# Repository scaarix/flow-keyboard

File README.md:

# Flow
An open source split mechanical keyboard powered by [Ergogen](https://github.com/ergogen/ergogen) and kicad
## The board:

# Updates
- REBUILDING THE DESIGN FROM THE GROUND UP
I didn't really like where I was going with this keyboard design and wanted to change the overall look and feel of the keyboard and the features that I want with this board
# Features
- Hotswappable with mx-style switches
- Flippable PCB
- 4 Key Thumb Cluster

## TODO
- [ ] Finish layout (ergogen)
- [ ] Make keyboard outline (ergogen) 
- [ ] Create pcb (ergogen)

# Goals
- Have hotswap with choc, kailh box etc.
- Be wireless
- Have RGB if I can actually configure it properly

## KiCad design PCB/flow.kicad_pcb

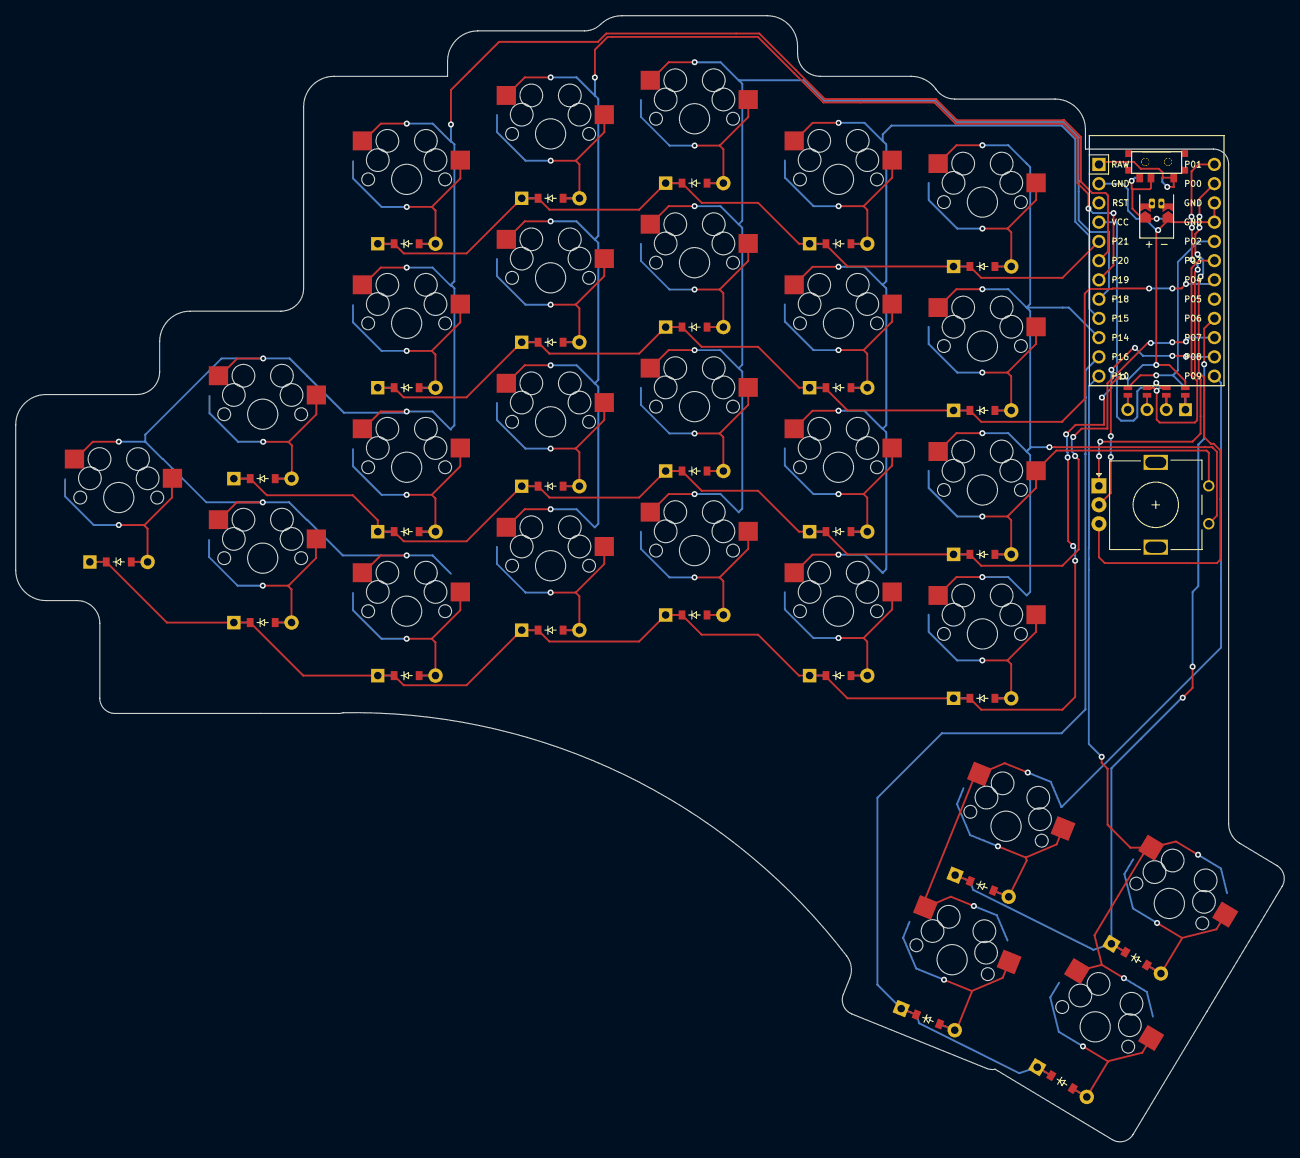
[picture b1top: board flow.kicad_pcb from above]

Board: 2 copper layers, 167.4 x 148.6 mm, 68 parts (0 on the bottom side), 52 nets.

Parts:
D1, D2, D3, D4, D5, D6, D7, D8, D9, D10, D11, D12, D13, D14, D15, D16, D17, D18, D19, D20, D21, D22, D23, D24, D25, D26, D27: ComboDiode
J1, J2, J3, J4, J5, J6, J7, J8: Jumper
JST1: PicoBlade_Power_Reversible
MCU1: ProMicro
OLED1: OLED; OLED_headers
ROT1: rotary_encoder
S1, S2, S3, S4, S5, S6, S7, S8, S9, S10, S11, S12, S13, S14, S15, S16, S17, S18, S19, S20, S21, S22, S23, S24, S25, S26, S27: MX
T1, T2: SPDT_C128955

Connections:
1_bottom: D24.2, S24.1
1_top: D25.2, S25.1
2_bottom: D26.2, S26.1
2_top: D27.2, S27.1
BAT+: JST1.1, T1.2, T2.1
GND: J4.2, J5.2, JST1.1, MCU1.2, MCU1.15, MCU1.16, ROT1.C
P0: MCU1.14, ROT1.B
P1: MCU1.13, ROT1.A
P2: J1.2, J8.2, MCU1.17
P3: J2.2, J7.2, MCU1.18
P4: D6.1, D10.1, D14.1, D18.1, D22.1, MCU1.19
P6: D25.1, D27.1, MCU1.21
P7: D3.1, D5.1, D9.1, D13.1, D17.1, D21.1, MCU1.22
P8: D1.1, D2.1, D4.1, D8.1, D12.1, D16.1, D20.1, MCU1.23
P9: MCU1.24, S24.2, S25.2
P10: MCU1.12, S26.2, S27.2
P14: MCU1.10, ROT1.2, S20.2, S21.2, S22.2, S23.2
P15: MCU1.9, S16.2, S17.2, S18.2, S19.2
P16: D24.1, D26.1, MCU1.11
P18: MCU1.8, S12.2, S13.2, S14.2, S15.2
P19: MCU1.7, S8.2, S9.2, S10.2, S11.2
P20: MCU1.6, S1.2, S2.2, S3.2, S4.2, S5.2, S6.2, S7.2
P21: D7.1, D11.1, D15.1, D19.1, D23.1, MCU1.5
RAW: MCU1.1, T1.1, T2.2
VCC: J3.2, J6.2, MCU1.4
far_bottom: D20.2, S20.1
far_home: D21.2, ROT1.1, S21.1
far_num: D23.2, S23.1
far_top: D22.2, S22.1
index_bottom: D16.2, S16.1
index_home: D17.2, S17.1
index_num: D19.2, S19.1
index_top: D18.2, S18.1
middle_bottom: D12.2, S12.1
middle_home: D13.2, S13.1
middle_num: D15.2, S15.1
middle_top: D14.2, S14.1
oled1: J1.1, J5.1, OLED1.4
oled2: J2.1, J6.1, OLED1.3
oled3: J3.1, J7.1, OLED1.2
oled4: J4.1, J8.1, OLED1.1
pinkie_bottom: D4.2, S4.1
pinkie_home: D5.2, S5.1
pinkie_num: D7.2, S7.1
pinkie_top: D6.2, S6.1
ring_bottom: D8.2, S8.1
ring_home: D9.2, S9.1
ring_num: D11.2, S11.1
ring_top: D10.2, S10.1
single_bottom: D1.2, S1.1
tab_bottom: D2.2, S2.1
tab_home: D3.2, S3.1

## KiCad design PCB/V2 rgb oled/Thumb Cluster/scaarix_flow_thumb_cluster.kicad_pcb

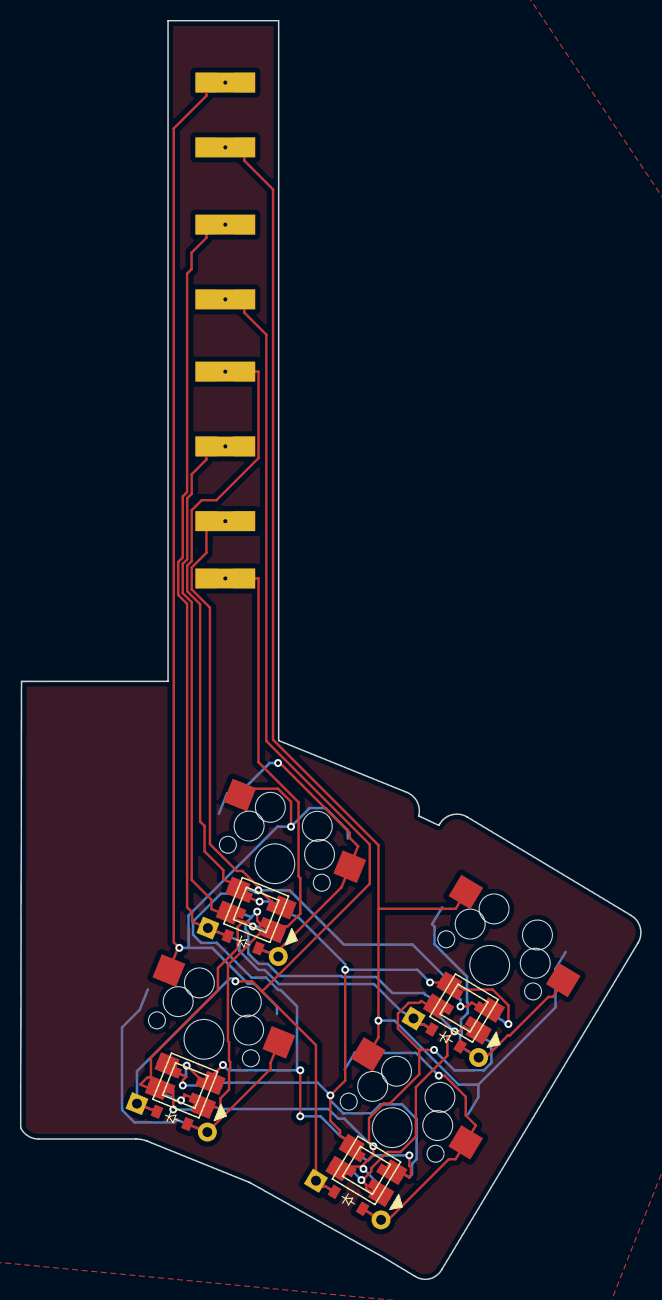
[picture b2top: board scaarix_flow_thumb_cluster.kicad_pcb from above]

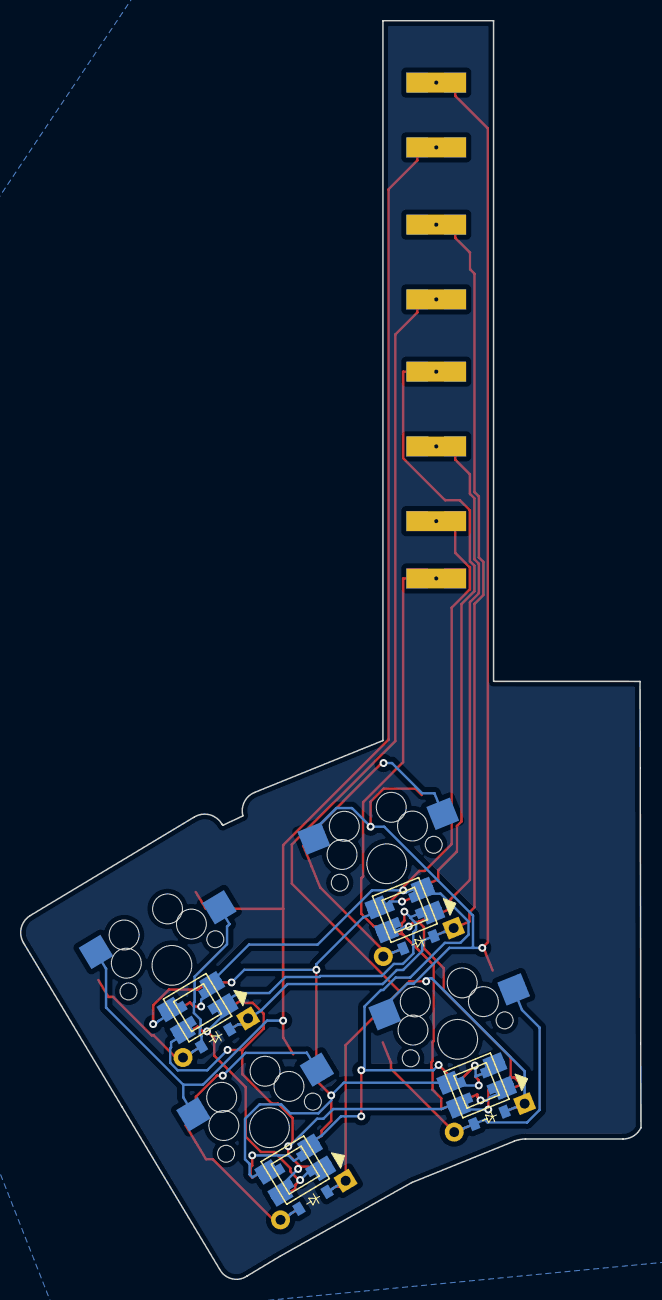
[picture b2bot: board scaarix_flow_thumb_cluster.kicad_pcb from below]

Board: 2 copper layers, 62.2 x 126.3 mm, 17 parts (5 on the bottom side), 12 nets.

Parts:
D24, D25, D26, D27: ComboDiode
J2: Conn_01x06; bridge
LED24, LED25, LED26, LED27, LED51, LED52, LED53, LED54: WS2812B
S24, S25, S26, S27: MX

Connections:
1_bottom: D24.2, S24.1
1_top: D25.2, S25.1
2_bottom: D26.2, S26.1
2_top: D27.2, S27.1
D1: J2.6, LED24.2, LED24.22, LED25.2, LED25.22, LED26.2, LED26.22, LED27.2, LED27.22, LED51.2, LED51.22, LED52.2, LED52.22, LED53.2, LED53.22, LED54.2, LED54.22
GND: J2.8 (Pin_6), LED24.3, LED24.33, LED25.3, LED25.33, LED26.3, LED26.33, LED27.3, LED27.33, LED51.3, LED51.33, LED52.3, LED52.33, LED53.3, LED53.33, LED54.3, LED54.33
P1: J2.7 (Pin_6), LED24.4, LED24.44, LED25.4, LED25.44, LED26.4, LED26.44, LED27.4, LED27.44, LED51.4, LED51.44, LED52.4, LED52.44, LED53.4, LED53.44, LED54.4, LED54.44
P10: J2.1, S24.2, S25.2
P16: J2.2, S26.2, S27.2
P18: D25.1, D27.1, J2.3
P19: D24.1, D26.1, J2.4
VCC: J2.4, J2.5, LED24.1, LED24.11, LED25.1, LED25.11, LED26.1, LED26.11, LED27.1, LED27.11, LED51.1, LED51.11, LED52.1, LED52.11, LED53.1, LED53.11, LED54.1, LED54.11

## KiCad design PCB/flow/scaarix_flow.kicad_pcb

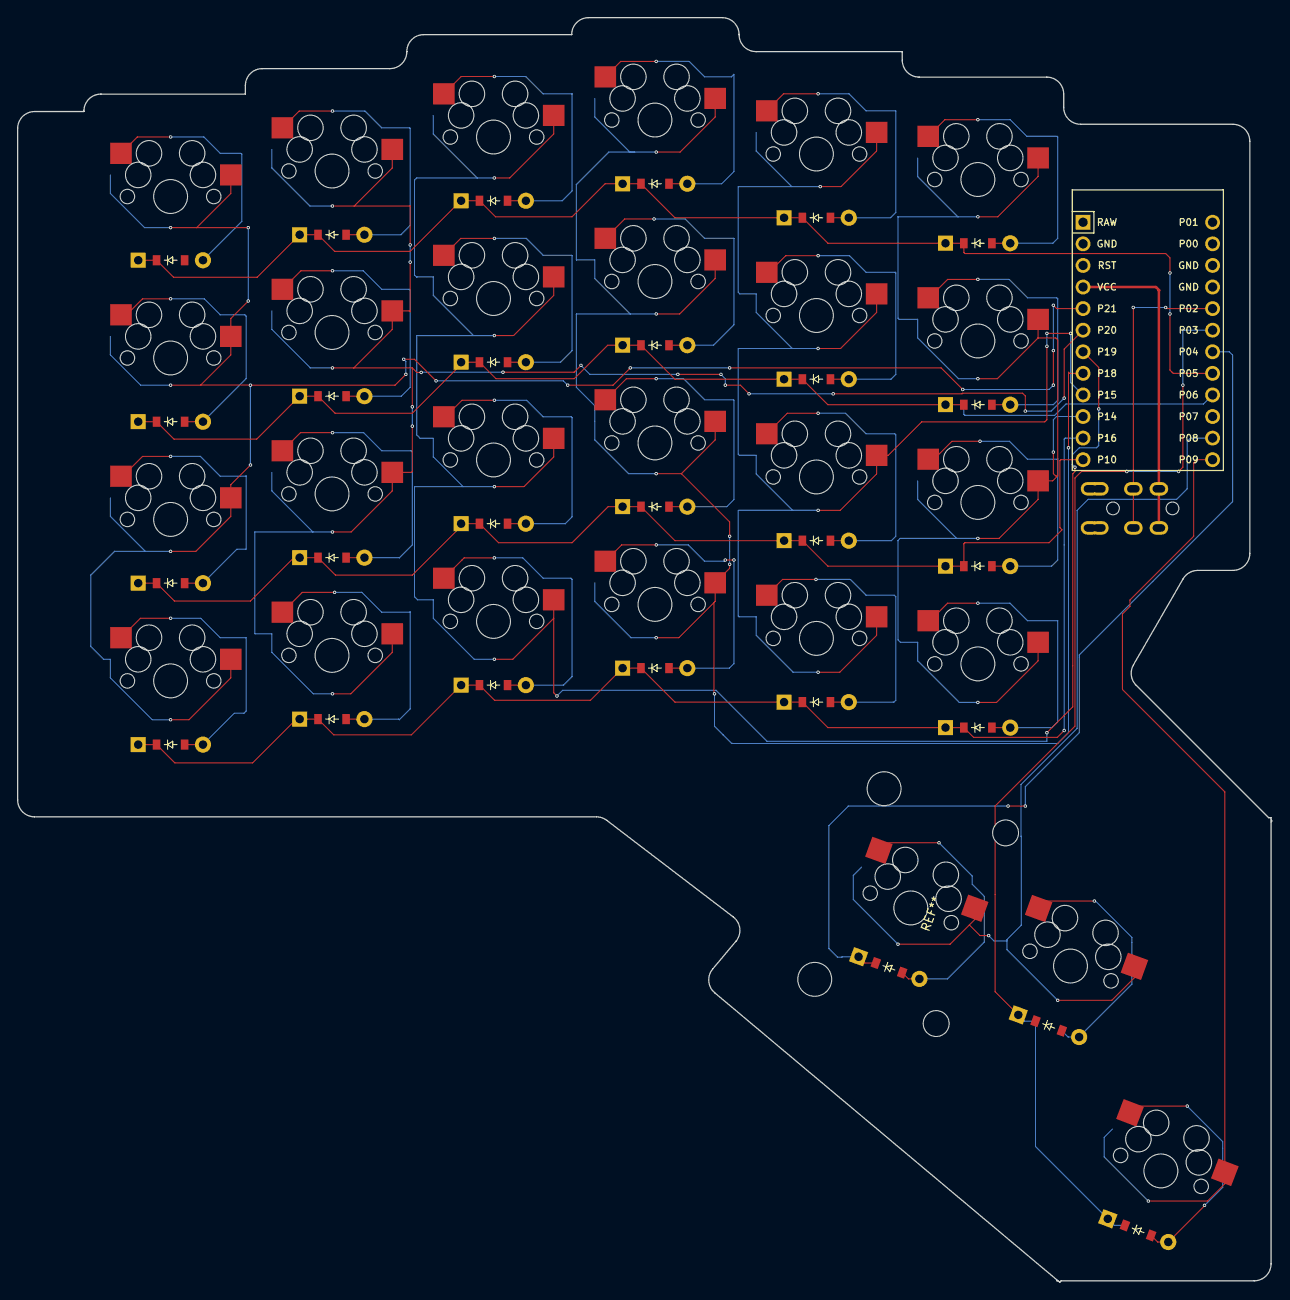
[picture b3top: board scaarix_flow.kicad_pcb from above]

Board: 2 copper layers, 147.6 x 148.8 mm, 55 parts (0 on the bottom side), 42 nets.

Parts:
D1, D2, D3, D4, D5, D6, D7, D8, D9, D10, D11, D12, D13, D14, D15, D16, D17, D18, D19, D20, D21, D22, D23, D24, D25, D26, D27: ComboDiode
MCU1: ProMicro
S1, S2, S3, S4, S5, S6, S7, S8, S9, S10, S11, S12, S13, S14, S15, S16, S17, S18, S19, S20, S21, S22, S23, S24, S25, S26, S27: MX

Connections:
1_bottom: D25.1, D25.2, S25.2
1_top: D26.1, D26.2, S26.2
2_top: D27.1, D27.2, S27.2
GND: MCU1.2, MCU1.15, MCU1.16
P3: D26.1, D26.2, D27.1, D27.2, MCU1.18
P4: D25.1, D25.2, MCU1.19
P5: D4.1, D4.2, D8.1, D8.2, D12.1, D12.2, D16.1, D16.2, D20.1, D20.2, D24.1, D24.2, MCU1.20
P6: D3.1, D3.2, D7.1, D7.2, D11.1, D11.2, D15.1, D15.2, D19.1, D19.2, D23.1, D23.2, MCU1.21
P8: MCU1.23, S25.1, S26.1
P9: MCU1.24, S27.1
P10: D2.1, D2.2, D6.1, D6.2, D10.1, D10.2, D14.1, D14.2, D18.1, D18.2, D22.1, D22.2, MCU1.12
P14: MCU1.10, S21.1, S22.1, S23.1, S24.1
P15: MCU1.9, S17.1, S18.1, S19.1, S20.1
P16: D1.1, D1.2, D5.1, D5.2, D9.1, D9.2, D13.1, D13.2, D17.1, D17.2, D21.1, D21.2, MCU1.11
P18: MCU1.8, S13.1, S14.1, S15.1, S16.1
P19: MCU1.7, S9.1, S10.1, S11.1, S12.1
P20: MCU1.6, S5.1, S6.1, S7.1, S8.1
P21: MCU1.5, S1.1, S2.1, S3.1, S4.1
far_bottom: D21.1, D21.2, S21.2
far_home: D22.1, D22.2, S22.2
far_num: D24.1, D24.2, S24.2
far_top: D23.1, D23.2, S23.2
index_bottom: D17.1, D17.2, S17.2
index_home: D18.1, D18.2, S18.2
index_num: D20.1, D20.2, S20.2
index_top: D19.1, D19.2, S19.2
middle_bottom: D13.1, D13.2, S13.2
middle_home: D14.1, D14.2, S14.2
middle_num: D16.1, D16.2, S16.2
middle_top: D15.1, D15.2, S15.2
pinkie_bottom: D5.1, D5.2, S5.2
pinkie_home: D6.1, D6.2, S6.2
pinkie_num: D8.1, D8.2, S8.2
pinkie_top: D7.1, D7.2, S7.2
ring_bottom: D9.1, D9.2, S9.2
ring_home: D10.1, D10.2, S10.2
ring_num: D12.1, D12.2, S12.2
ring_top: D11.1, D11.2, S11.2
tab_bottom: D1.1, D1.2, S1.2
tab_home: D2.1, D2.2, S2.2
tab_num: D4.1, D4.2, S4.2
tab_top: D3.1, D3.2, S3.2

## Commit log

2022-10-21 added trrs, fixed mcu changed pcb shape
2022-10-21 moved diodes and added space for screw holes
2022-10-21 added row nets
2022-10-22 made pcb tops bigger so keycaps weren't atop of case
2022-10-22 fixed fillet
2022-10-27 fixed diodes
2022-11-01 fixed pcb and trrs placement
2022-11-05 moved thumb cluster for stabs
2022-12-10 Changed routing a little and generated gerbers
2022-12-11 cleaned up a little
2022-12-11 Changed footprint and rerouted
    Used a different footprint that wasn't hotswappable. Changed it and Re-routed
2022-12-11 Fixed stabilizers
    Stab orientation was wrong
2023-01-07 ergogen v4 version DONT USE SINCE IT IS BROKEN!
2023-01-07 help me fix this PLEASE
2023-01-26 finnally stopped procrastinating migration to v4
    this is going to take a while. Bare with me
2023-01-27 made switches and diodes actually appear
2023-01-27 started working on mcu placement
2023-01-29 starting to work on aesthetics of pcb
    may change to rp2040 for a diode-less design
    tbd
2023-01-30 testing purposes
2023-01-30 fixed oled TODO: change oled pins
2023-01-30 changed to be up to date
2023-01-30 FINISHED
    This version is v2 wired, oled and non rgb
2023-01-30 Create V2 RGB OLED
    Removed 1 tab key, moved other tab key, changed thumb cluster and I am happy with the results
2023-01-31 Create V2 Non RGB Oled
2023-02-01 routed pcb with freerouting and generated gerbers for pcb printing
2023-02-01 learned how to spell
2023-02-01 separated thumb cluster, main body and bridge
    this is used to for actually printing the pcb :)
2023-02-01 added gerbers that I forgot to add
2023-02-09 added switch plates & their gerbers
2023-02-09 added switch plate & gerbers
2023-03-23 Updated Photo
2023-05-14 updated todos, and added some updates
2023-05-14 added updated version of the keyboard design
    Rebuilding what was previously bad and needed work. Now adding Oled, and wireless
2023-05-15 fixed slider and added BAT+ to the battery
2023-05-16 added rotary needs fixing
2023-05-16 fixed the "from" in the rotary encoder. Have to add diodes now
2023-05-18 fixed rotary encoder position
2023-05-22 added jumpers for oled and added second side to on/off switch
2023-05-24 fixed outline
2023-05-24 moved
2023-05-24 moved files
2023-05-24 moved gerbers
2023-05-25 fixed outlines
2023-05-25 Update flow_keyboard
2023-05-25 Rename flow_keyboard to flow_keyboard.yaml
2023-05-26 fixed oled jumpers
2023-05-26 Create temp
2023-05-26 fixed oled positioning and jumper positioning
2023-05-27 fixed rotary encoder positioning
2023-05-29 fixed rotary encoder pins
2023-05-29 fixes
2023-05-29 changed pins
2023-05-29 more fixes
2023-06-01 fixed board outline
2023-06-29 changed sizing to accommodate screw holes
2023-08-25 added case bottom
2023-08-25 added screw holes
2023-08-25 started working on plate
